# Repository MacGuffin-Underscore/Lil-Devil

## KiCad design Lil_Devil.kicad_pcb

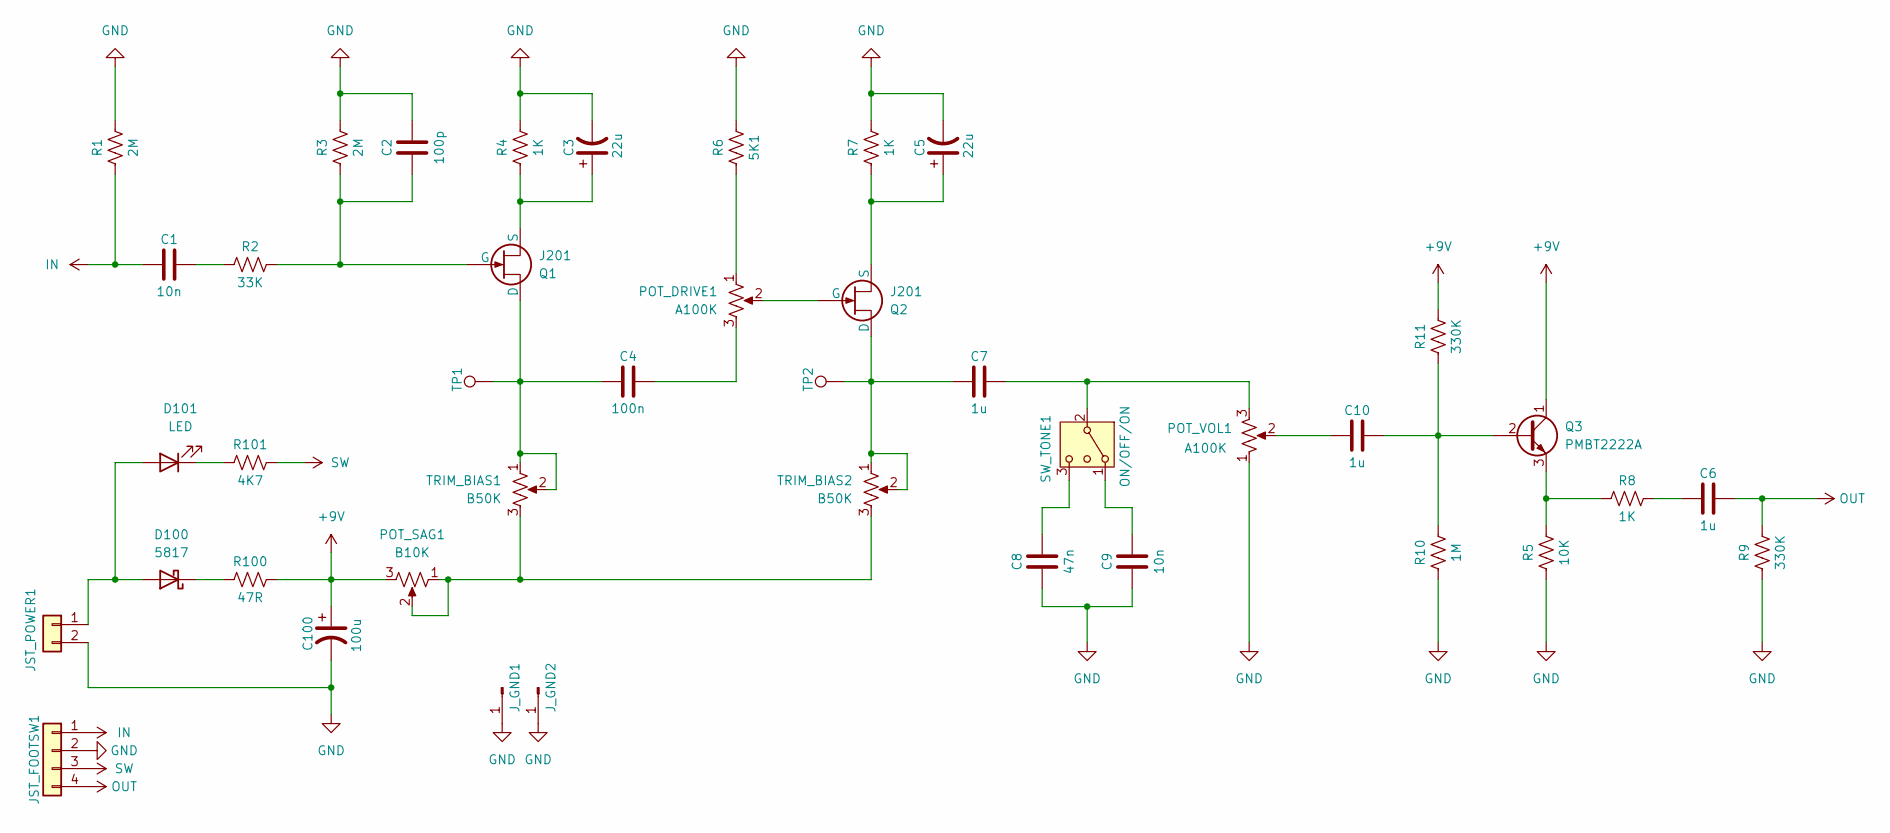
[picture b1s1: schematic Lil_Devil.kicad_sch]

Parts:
C1, C9: 10n; C_Film_L7.2_W2.5_SilkVal
C2: 100p; C_Film_L7.2_W2.5_SilkVal
C3, C5: 22u; C_Electro_D6.3mm_P2.50mm_SilkVal
C4: 100n; C_Film_L7.2_W5.0_SilkVal
C6, C10: 1u; C_Film_L7.2_W5.0_SilkVal
C7: 1u; C_Film_L7.2_W5.0_SilkRef
C8: 47n; C_Film_L7.2_W2.5_SilkVal
C100: 100u; C_Electro_D6.3mm_P2.50mm_SilkVal
D100: 5817; D_DO-35_L7.62mm_Horz_SilkVal
D101: LED; LED_P3
JST_FOOTSW1: Conn_01x04; JST_XH_B4B-XH-AM_1x04_P2.50mm_Vertical
JST_POWER1: Conn_01x02; JST_XH_B2B-XH-AM_1x02_P2.50mm_Vertical
J_GND1, J_GND2: Conn_01x01_Pin; Wire_Hookup
POT_DRIVE1: A100K; Pot_16mm_ShaftCentered_OffBoard
POT_SAG1: B10K; Pot_16mm_ShaftCentered_OffBoard
POT_VOL1: A100K; Pot_16mm_ShaftCentered_OffBoard
Q1, Q2: J201; TO-92-3_FormedLeads_SilkVal
Q3: PMBT2222A; TO-92-3_FormedLeads_SilkVal
R1, R3: 2M; R_Axial_L6.3_D2.5_P7.62_Horizontal_SilkVal
R2: 33K; R_Axial_L6.3_D2.5_P7.62_Horizontal_SilkVal
R4, R7, R8: 1K; R_Axial_L6.3_D2.5_P7.62_Horizontal_SilkVal
R5: 10K; R_Axial_L6.3_D2.5_P7.62_Horizontal_SilkVal
R6: 5K1; R_Axial_L6.3_D2.5_P7.62_Horizontal_SilkVal
R9, R11: 330K; R_Axial_L6.3_D2.5_P7.62_Horizontal_SilkVal
R10: 1M; R_Axial_L6.3_D2.5_P7.62_Horizontal_SilkVal
R100: 47R; R_Axial_L6.3_D2.5_P7.62_Horizontal_SilkVal
R101: 4K7; R_Axial_L6.3_D2.5_P7.62_Horizontal_SilkVal
SW_TONE1: ON/OFF/ON; Switch_Toggle_SPDT_Mini_SolderLug
TP1, TP2: TestPoint; TestPoint_Keystone_5010-5014_Multipurpose
TRIM_BIAS1, TRIM_BIAS2: B50K; Pot_Trim_7x6.6mm_T73YE

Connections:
+9V: C100.1, POT_SAG1.3, Q3.1 (C), R11.2, R100.2
GND: C2.1, C3.2, C5.2, C8.2, C9.2, C100.2, JST_FOOTSW1.2, JST_POWER1.2, J_GND1.1, J_GND2.1, POT_VOL1.1, R1.2, R3.2, R4.2, R5.1, R6.2, R7.2, R9.1, R10.1
IN: C1.2, JST_FOOTSW1.1, R1.1
unnamed: C1.1, R2.1
unnamed: C4.1, POT_DRIVE1.3
unnamed: C6.2, R8.2
unnamed: C9.1, SW_TONE1.1
unnamed: C10.2, POT_VOL1.2
unnamed: D100.2 (A), D101.2 (A), JST_POWER1.1
unnamed: D100.1 (K), R100.1
unnamed: D101.1 (K), R101.1
unnamed: POT_DRIVE1.1, R6.1
unnamed: POT_SAG1.1, POT_SAG1.2, TRIM_BIAS1.3, TRIM_BIAS2.3
unnamed: C4.2, Q1.1 (D), TP1.1, TRIM_BIAS1.1, TRIM_BIAS1.2
unnamed: C2.2, Q1.3 (G), R2.2, R3.1
unnamed: C3.1, Q1.2 (S), R4.1
unnamed: C7.2, Q2.1 (D), TP2.1, TRIM_BIAS2.1, TRIM_BIAS2.2
unnamed: POT_DRIVE1.2, Q2.3 (G)
unnamed: C5.1, Q2.2 (S), R7.1
unnamed: C10.1, Q3.2 (B), R10.2, R11.1
unnamed: Q3.3 (E), R5.2, R8.1
unnamed: C7.1, POT_VOL1.3, SW_TONE1.2 (3)
unnamed: C8.1, SW_TONE1.3 (4)
OUT: C6.1, JST_FOOTSW1.4, R9.2
SW: JST_FOOTSW1.3, R101.2

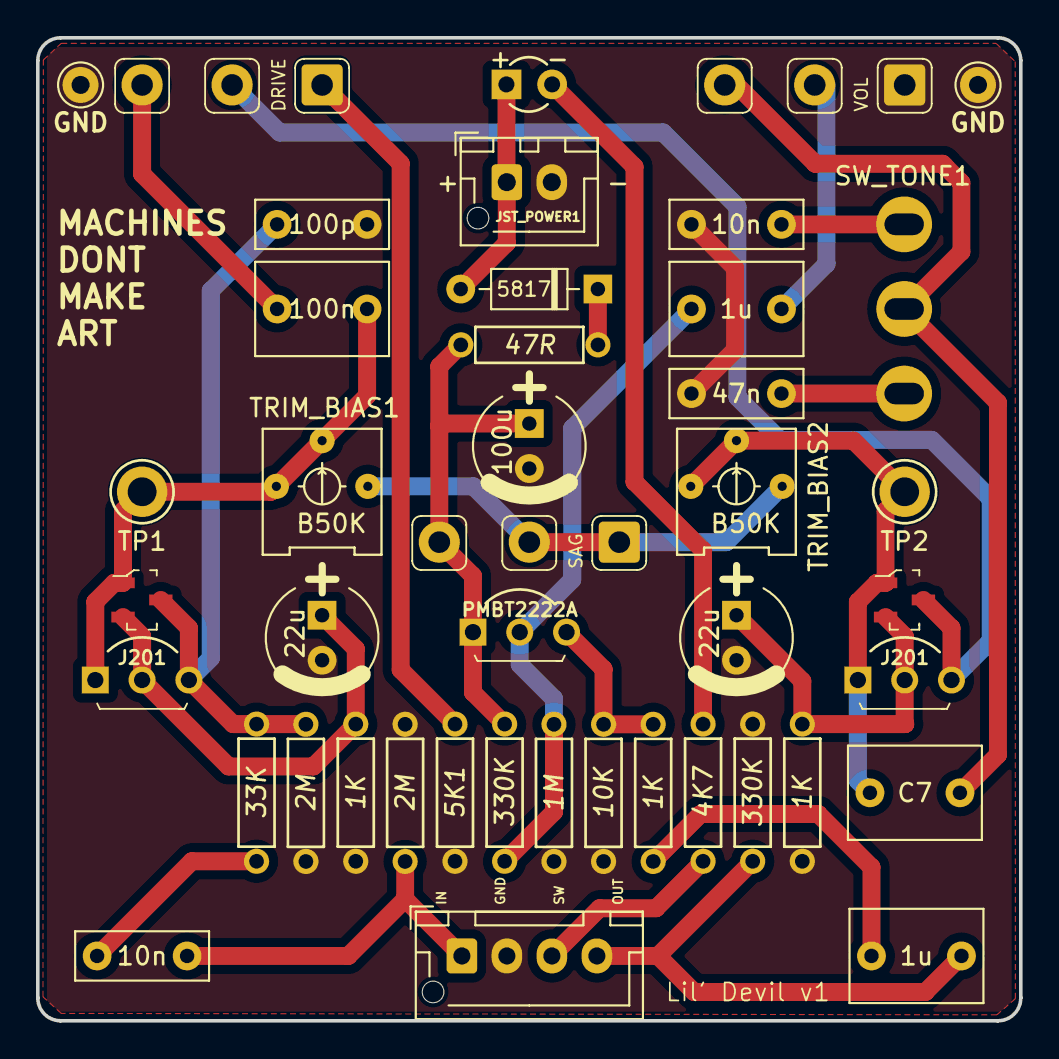
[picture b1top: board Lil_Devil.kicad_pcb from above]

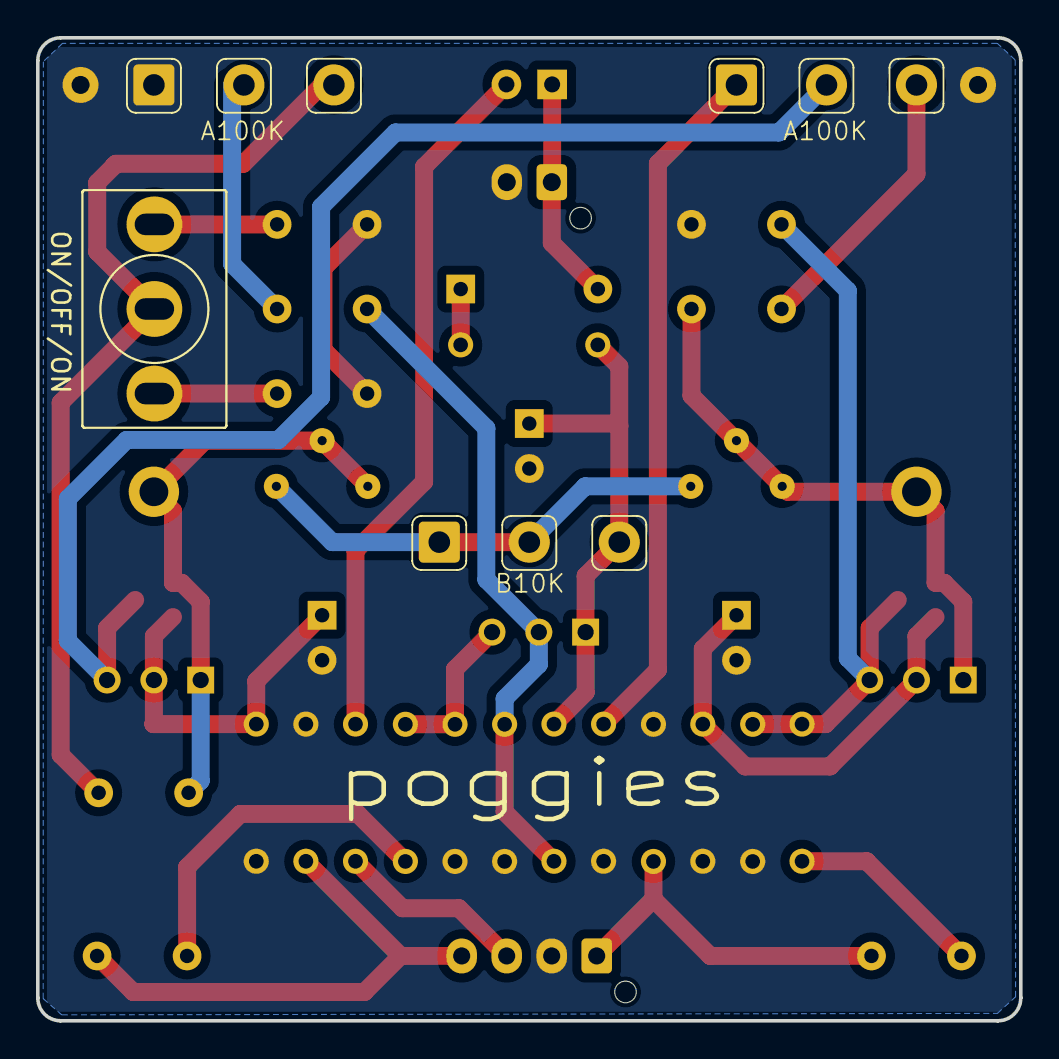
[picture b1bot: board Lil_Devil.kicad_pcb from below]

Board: 2 copper layers, 54.6 x 54.6 mm, 41 parts (4 on the bottom side), 25 nets.

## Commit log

2026-05-30 Delete LICENSE
    changing to CC
